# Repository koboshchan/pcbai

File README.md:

pcbai is an analog MNIST classifier built from discrete PCB neural-network boards.

boards/ contains only the final paid v2 sources, matching fabrication ZIPs and the current ADS carrier v3. boards/SHA256.json records exact source hashes. DC1 is four-layer and universal; build four copies using its separate DC1a through DC1d population CSVs. boards/bom/ holds the current assembly data and CSVs.

The motherboard needs the mandatory bottom bodge wire from JS1 B7 at (18.25, 44.27) mm to JS2 B7 at (18.25, 55.27) mm. Fit it before powering the stack. See boards/README.md for release-source and model-path notes.

scripts/ holds the current fabrication exporter, dimensions audit, corrected overlay utilities, BOM PDF builder and paid-board emulator harness. training/ holds MNIST training code, model checkpoints, layer weights, physical-model evaluations and required provenance inputs. The emulator itself lives separately at https://github.com/koboshchan/pcb-emu and is not vendored here.

renders/ contains current board images and the final v2 stack renders. pdfs/ contains the current BOM, corrected normal and clockwise/text-upright overview overlays, motherboard placement input and ADS etch mask. footprints/, 3dmodels/ and fp-lib-table retain the custom connector assets.

Old designs, routing experiments and stale outputs were deleted from the working tree, not archived. They remain available in Git history.

Run heavy training, simulation, CAD exports and rendering on KAT-BOX only. Generated output goes under ignored out/. Release sources and paid fabrication ZIPs are never overwritten by the exporter.

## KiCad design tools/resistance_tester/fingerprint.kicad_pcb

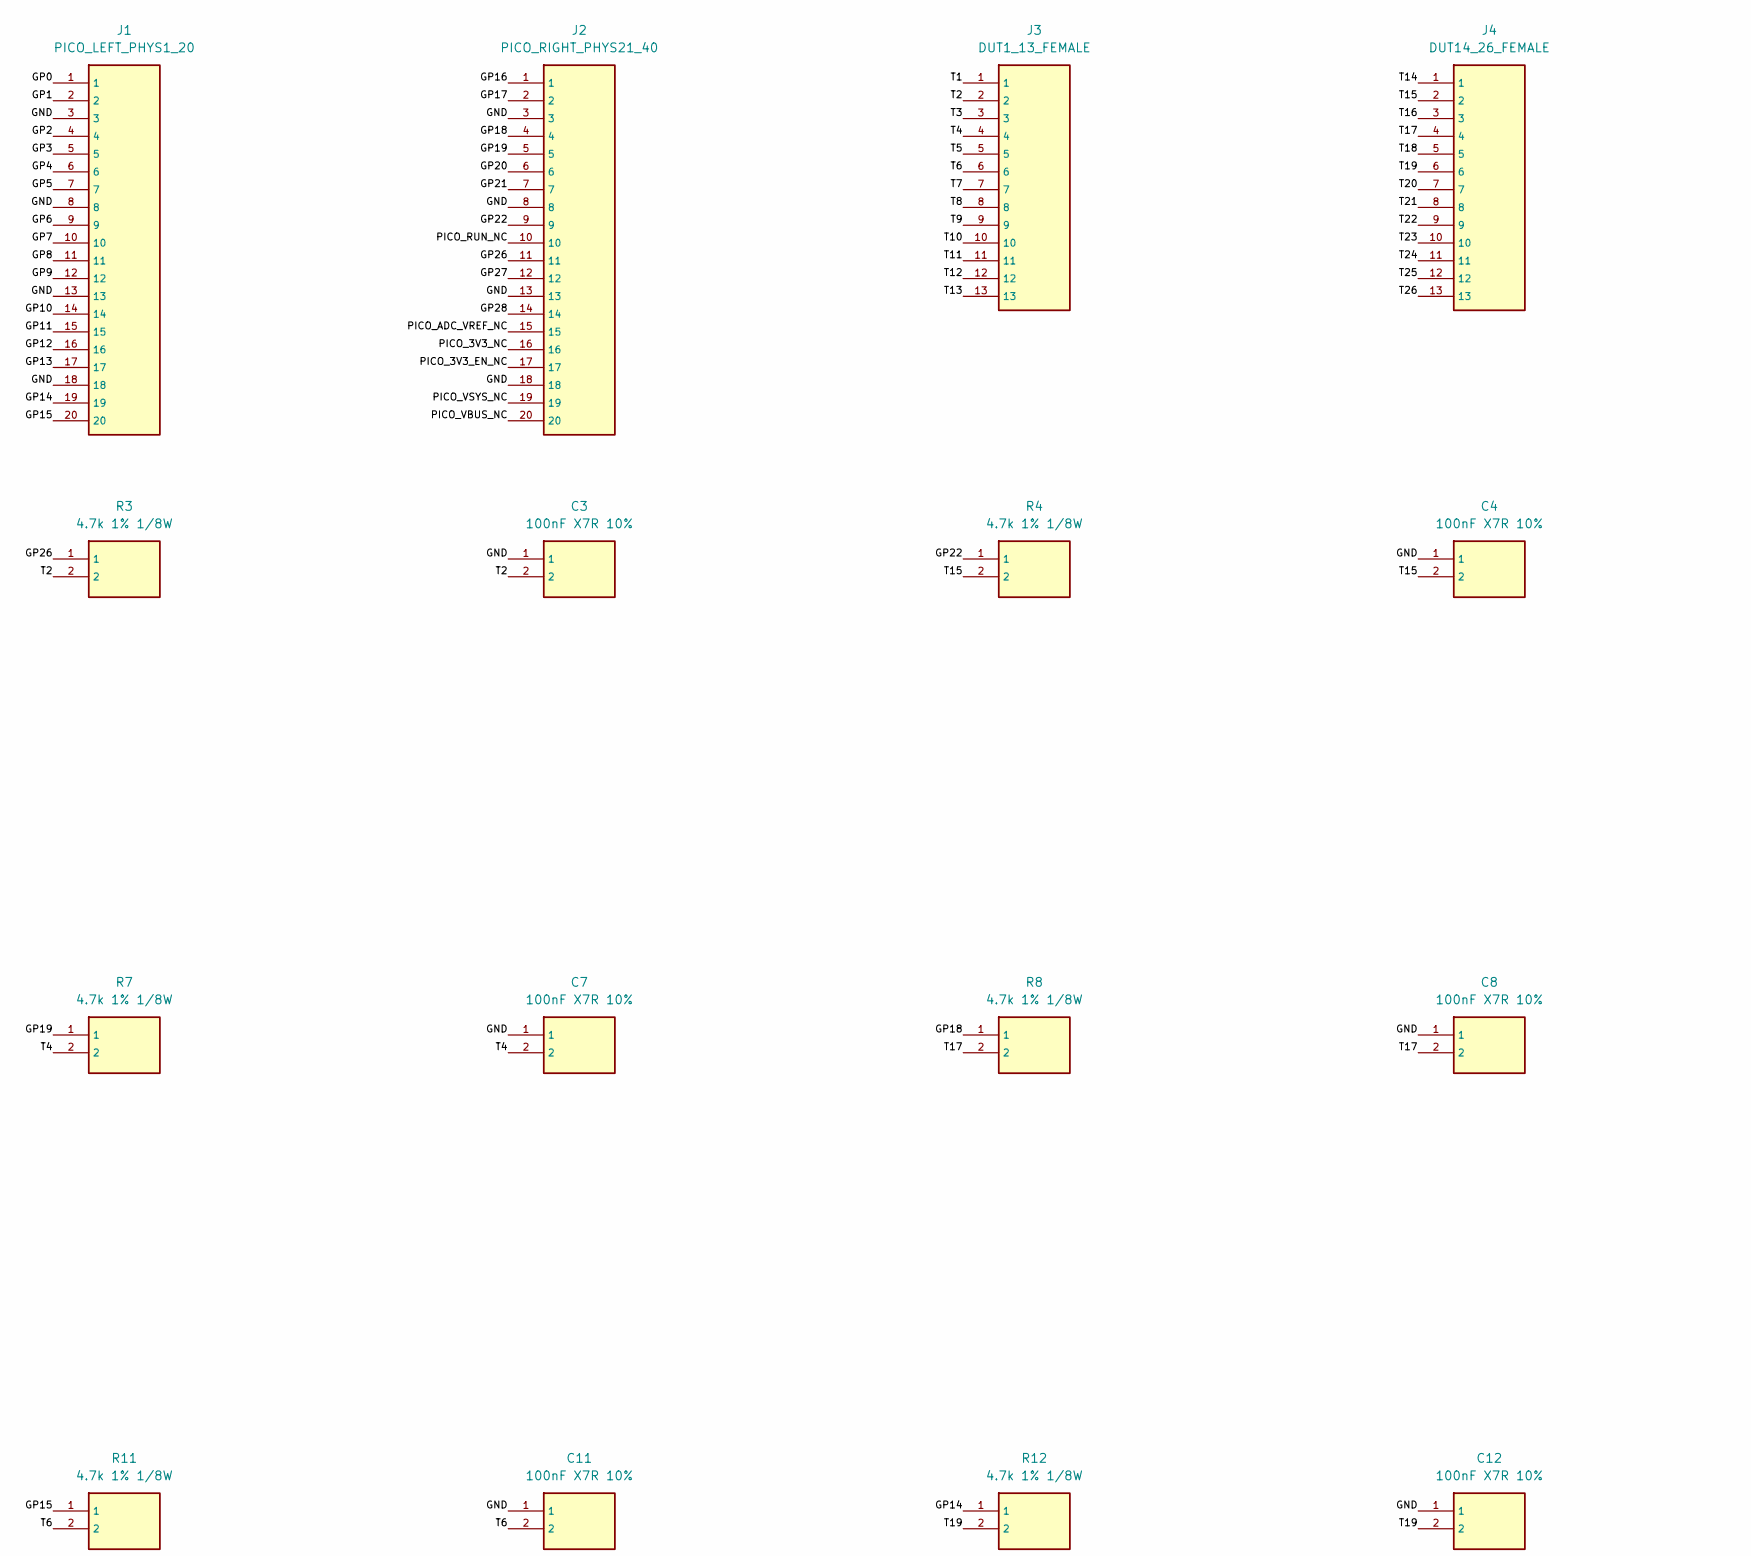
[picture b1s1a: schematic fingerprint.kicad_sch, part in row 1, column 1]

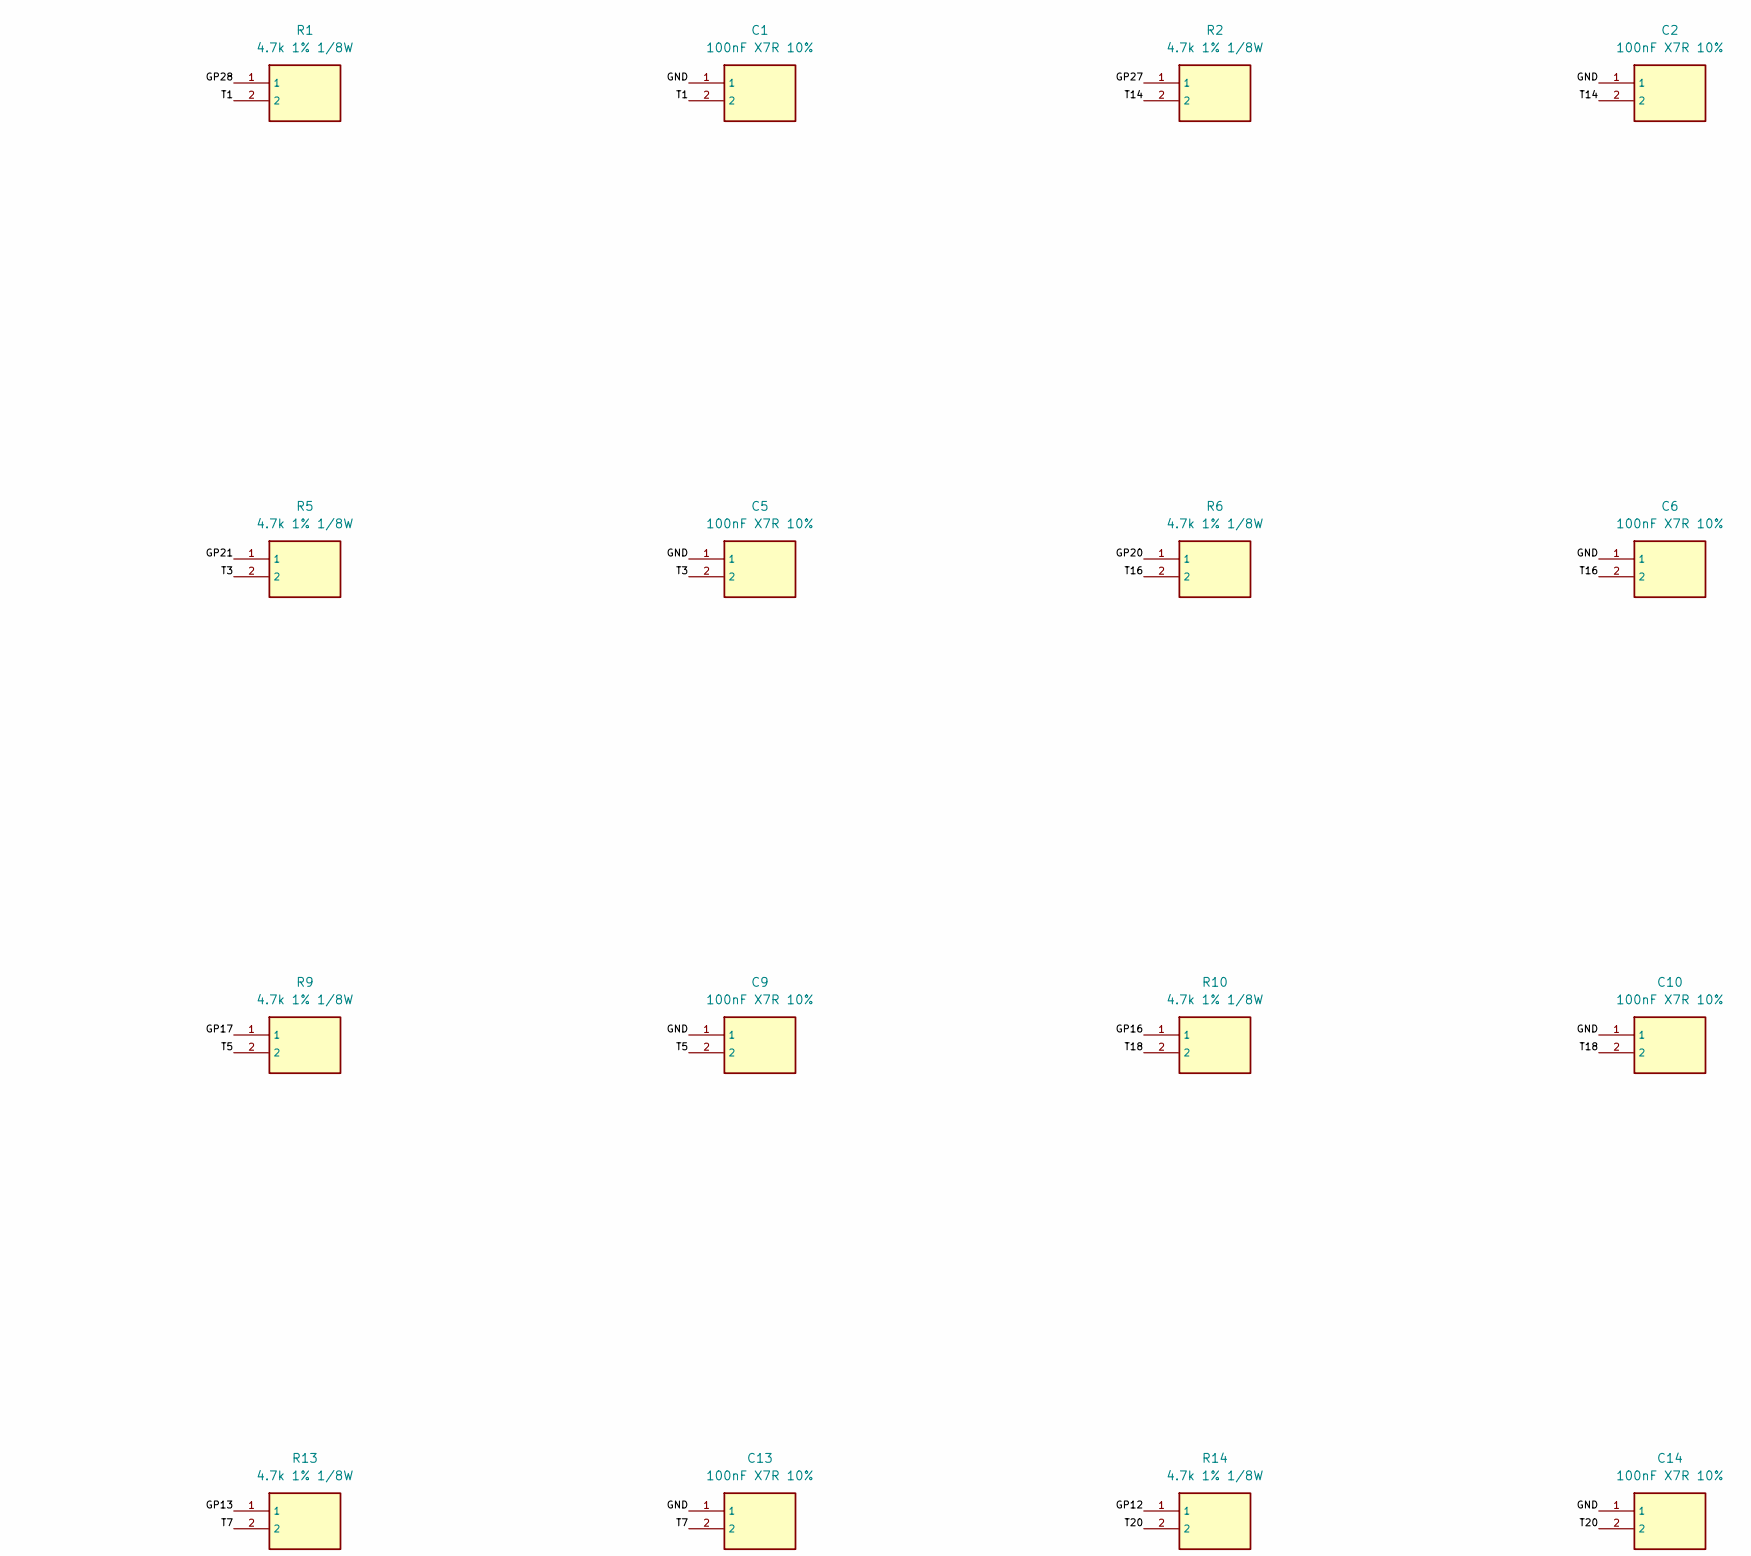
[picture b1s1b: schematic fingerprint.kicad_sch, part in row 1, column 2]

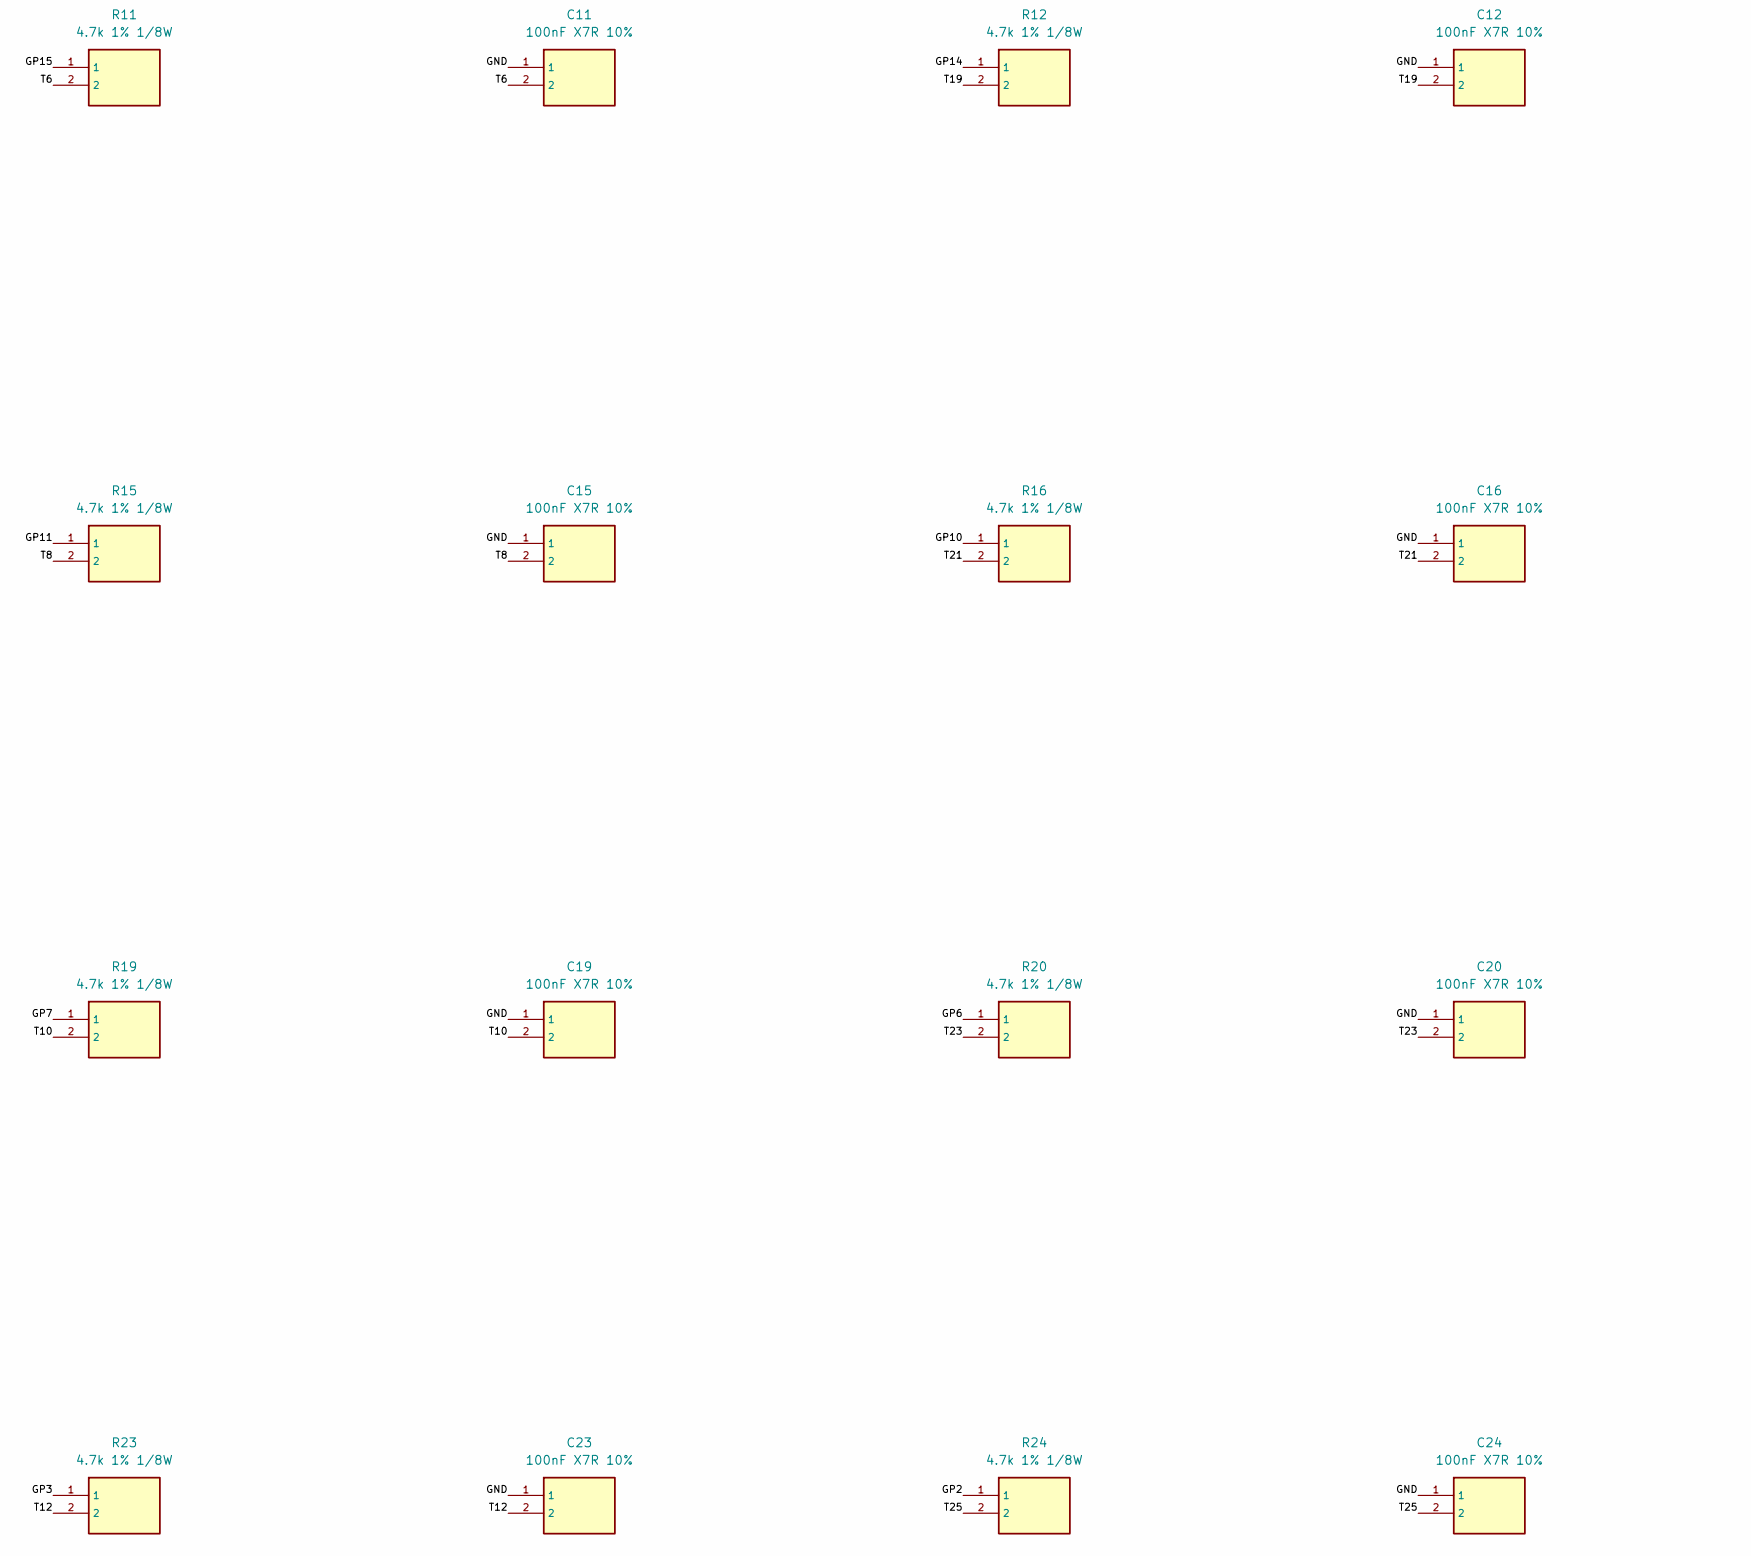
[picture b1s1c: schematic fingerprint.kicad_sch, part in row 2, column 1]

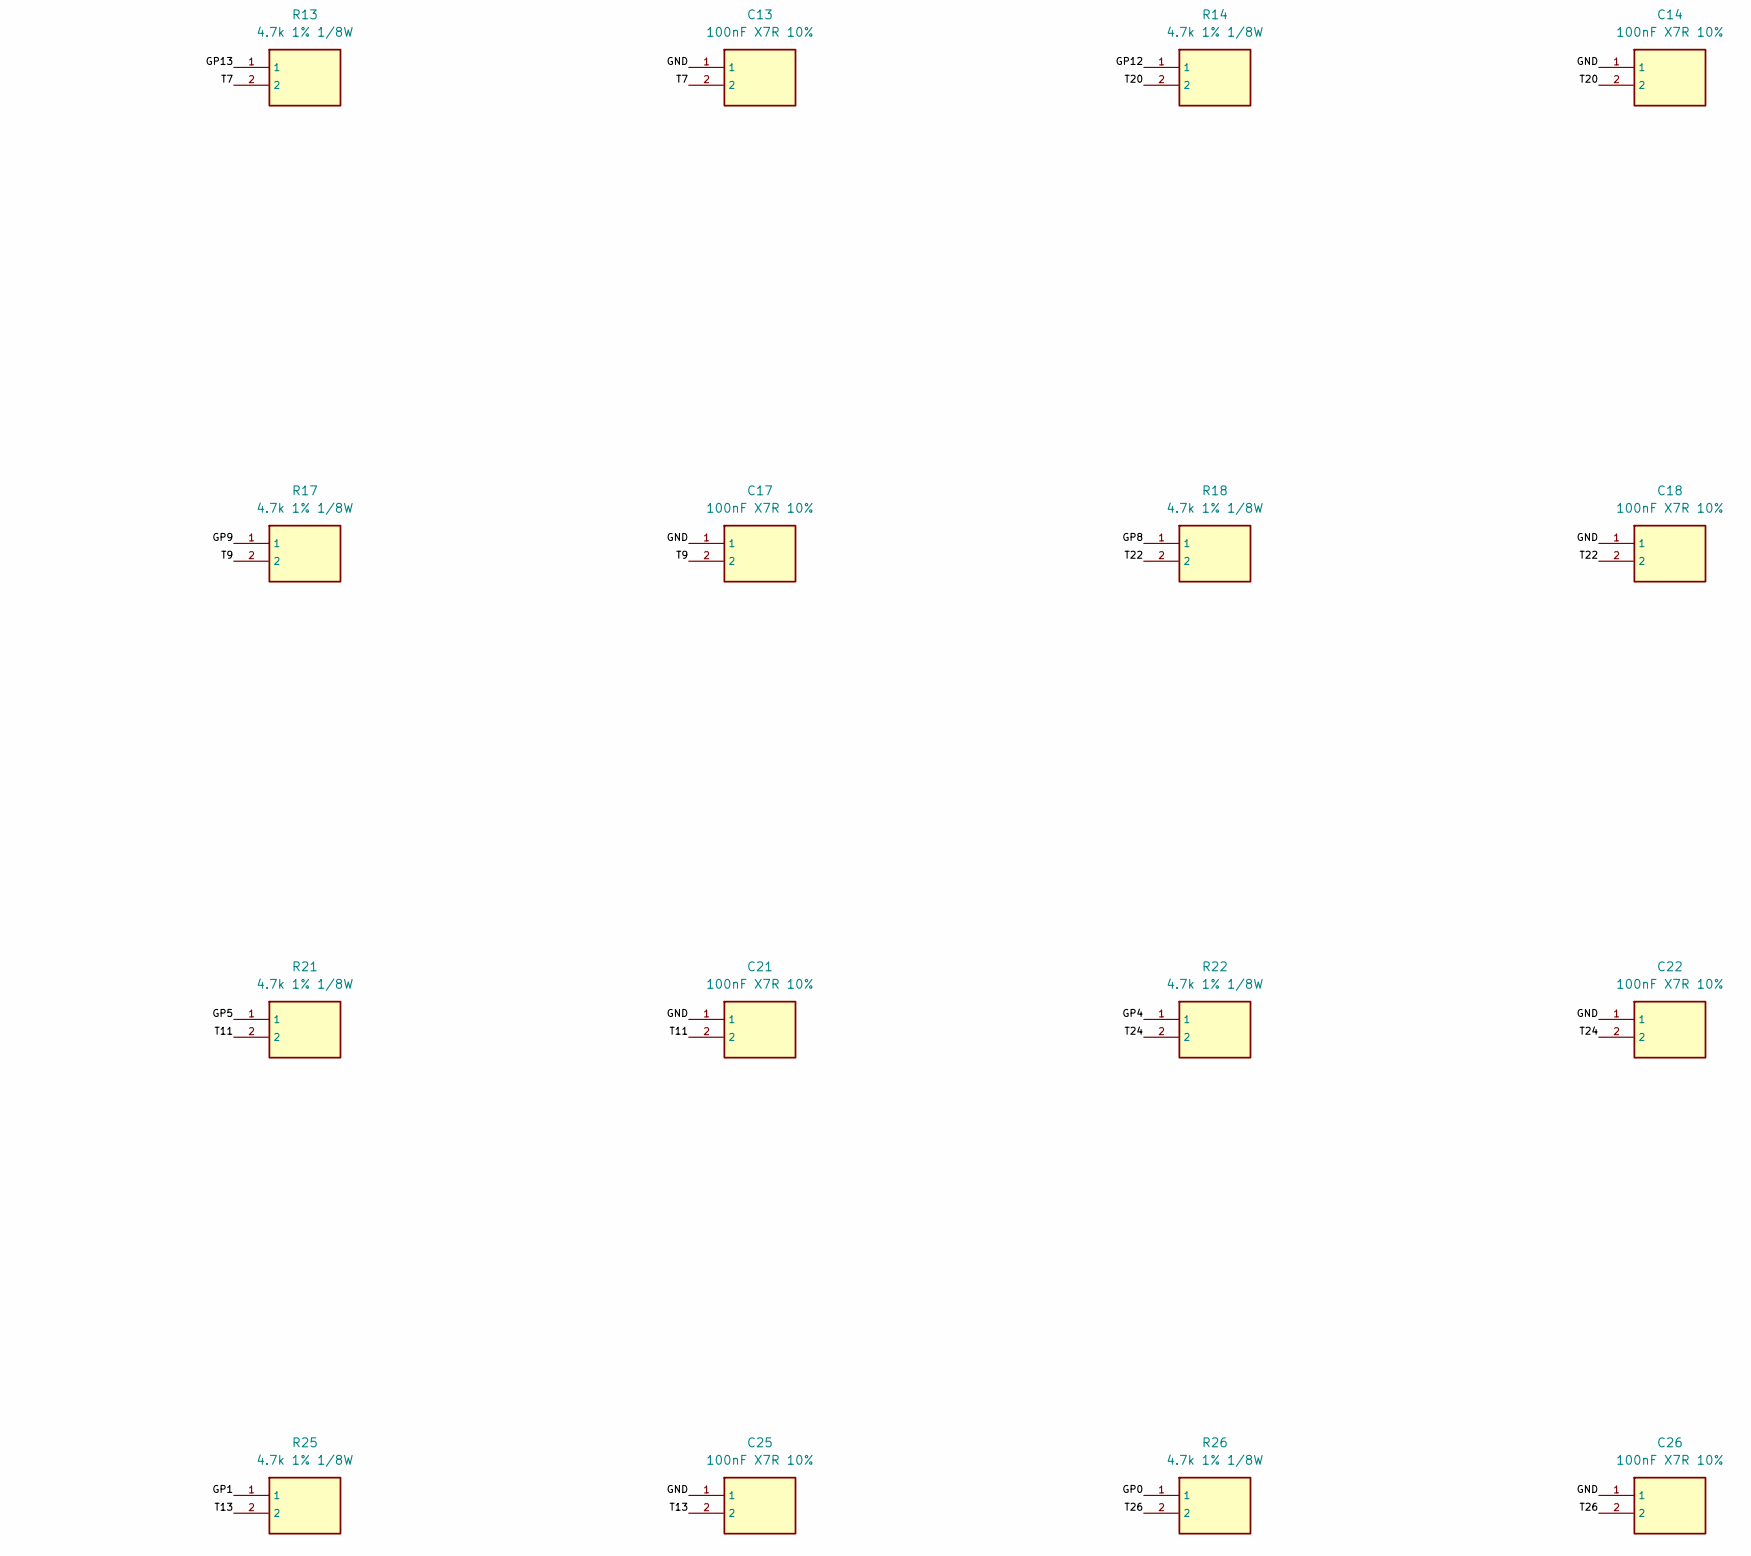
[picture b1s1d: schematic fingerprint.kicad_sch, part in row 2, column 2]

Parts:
C1, C2, C3, C4, C5, C6, C7, C8, C9, C10, C11, C12, C13, C14, C15, C16, C17, C18, C19, C20, C21, C22, C23, C24, C25, C26: 100nF X7R 10%; C_0805_2012Metric
J1: PICO_LEFT_PHYS1_20; Pico_1x20_female_oval_1.7x1.4 (embedded, rectangular pin 1)
J2: PICO_RIGHT_PHYS21_40; Pico_1x20_female_oval_1.7x1.4 (embedded, rectangular pin 1)
J3: DUT1_13_FEMALE; PinSocket_1x13_P2.54mm_Vertical_2x13_block_modified (embedd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
J4: DUT14_26_FEMALE; PinSocket_1x13_P2.54mm_Vertical_2x13_block_modified (embedd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
R1, R2, R3, R4, R5, R6, R7, R8, R9, R10, R11, R12, R13, R14, R15, R16, R17, R18, R19, R20, R21, R22, R23, R24, R25, R26: 4.7k 1% 1/8W; R_0805_2012Metric

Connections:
GND: C1.1, C2.1, C3.1, C4.1, C5.1, C6.1, C7.1, C8.1, C9.1, C10.1, C11.1, C12.1, C13.1, C14.1, C15.1, C16.1, C17.1, C18.1, C19.1, C20.1, C21.1, C22.1, C23.1, C24.1, C25.1, C26.1, J1.3, J1.8, J1.13, J1.18, J2.3, J2.8, J2.13, J2.18
GP0: J1.1, R26.1
GP1: J1.2, R25.1
GP2: J1.4, R24.1
GP3: J1.5, R23.1
GP4: J1.6, R22.1
GP5: J1.7, R21.1
GP6: J1.9, R20.1
GP7: J1.10, R19.1
GP8: J1.11, R18.1
GP9: J1.12, R17.1
GP10: J1.14, R16.1
GP11: J1.15, R15.1
GP12: J1.16, R14.1
GP13: J1.17, R13.1
GP14: J1.19, R12.1
GP15: J1.20, R11.1
GP16: J2.1, R10.1
GP17: J2.2, R9.1
GP18: J2.4, R8.1
GP19: J2.5, R7.1
GP20: J2.6, R6.1
GP21: J2.7, R5.1
GP22: J2.9, R4.1
GP26: J2.11, R3.1
GP27: J2.12, R2.1
GP28: J2.14, R1.1
PICO_3V3_EN_NC: J2.17
PICO_3V3_NC: J2.16
PICO_ADC_VREF_NC: J2.15
PICO_RUN_NC: J2.10
PICO_VBUS_NC: J2.20
PICO_VSYS_NC: J2.19
T1: C1.2, J3.1, R1.2
T2: C3.2, J3.2, R3.2
T3: C5.2, J3.3, R5.2
T4: C7.2, J3.4, R7.2
T5: C9.2, J3.5, R9.2
T6: C11.2, J3.6, R11.2
T7: C13.2, J3.7, R13.2
T8: C15.2, J3.8, R15.2
T9: C17.2, J3.9, R17.2
T10: C19.2, J3.10, R19.2
T11: C21.2, J3.11, R21.2
T12: C23.2, J3.12, R23.2
T13: C25.2, J3.13, R25.2
T14: C2.2, J4.1, R2.2
T15: C4.2, J4.2, R4.2
T16: C6.2, J4.3, R6.2
T17: C8.2, J4.4, R8.2
T18: C10.2, J4.5, R10.2
T19: C12.2, J4.6, R12.2
T20: C14.2, J4.7, R14.2
T21: C16.2, J4.8, R16.2
T22: C18.2, J4.9, R18.2
T23: C20.2, J4.10, R20.2
T24: C22.2, J4.11, R22.2
T25: C24.2, J4.12, R24.2
T26: C26.2, J4.13, R26.2

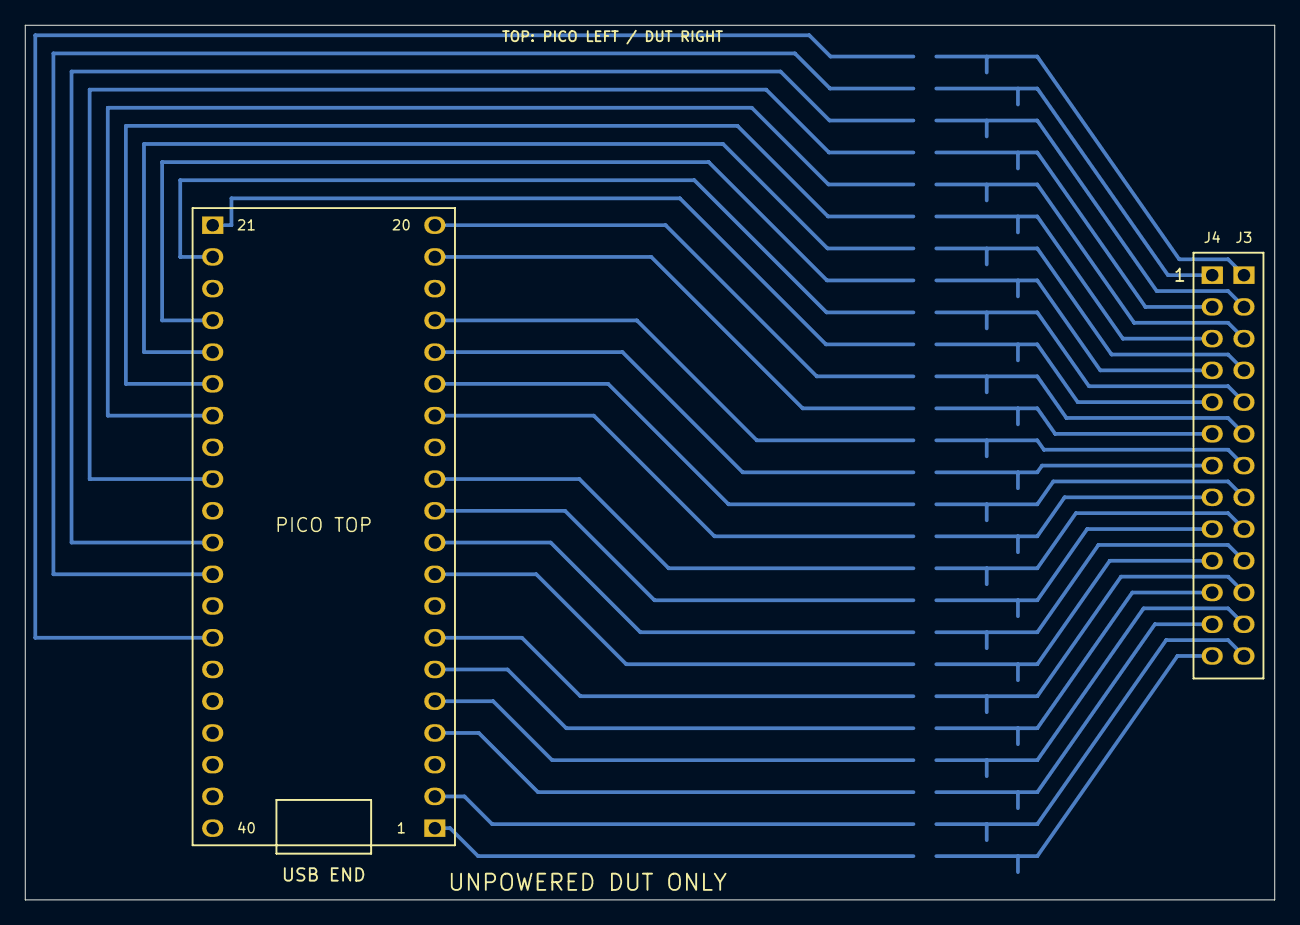
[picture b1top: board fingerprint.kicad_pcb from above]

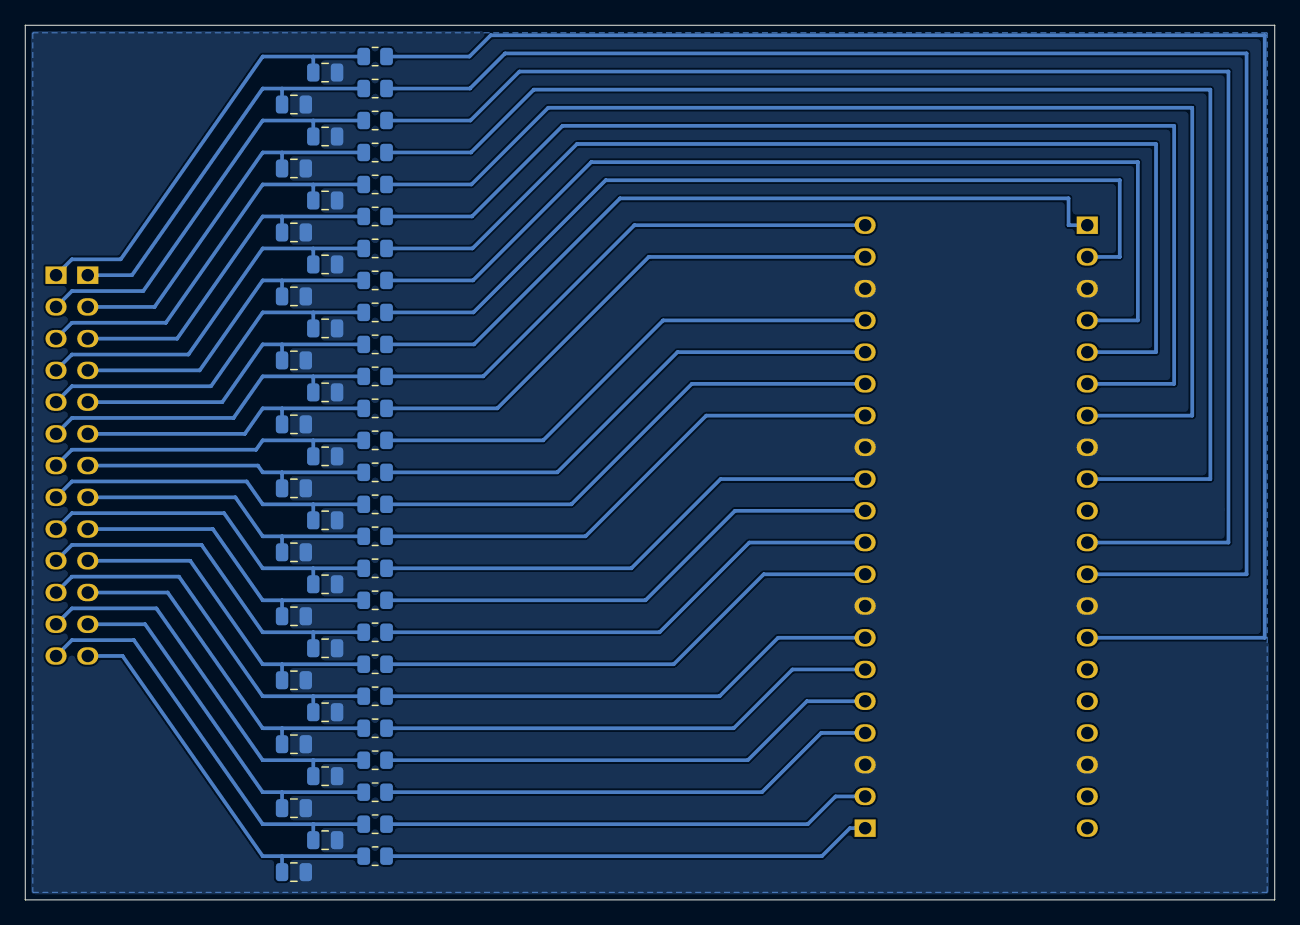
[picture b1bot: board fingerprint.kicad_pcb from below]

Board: 2 copper layers, 100.0 x 70.0 mm, 56 parts (52 on the bottom side), 53 nets.

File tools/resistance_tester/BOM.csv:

Reference,Value,Footprint,Side
J1,PICO_LEFT_PHYS1_20,"Pico_1x20_female_oval_1.7x1.4 (embedded, rectangular pin 1)",Top
J2,PICO_RIGHT_PHYS21_40,"Pico_1x20_female_oval_1.7x1.4 (embedded, rectangular pin 1)",Top
J3,DUT1_13_FEMALE,"PinSocket_1x13_P2.54mm_Vertical_2x13_block_modified (embedded, shared 2x13 silk box, abutting courtyards)",Top
J4,DUT14_26_FEMALE,"PinSocket_1x13_P2.54mm_Vertical_2x13_block_modified (embedded, shared 2x13 silk box, abutting courtyards)",Top
R1,4.7k 1% 1/8W,Resistor_SMD:R_0805_2012Metric,Bottom
C1,100nF X7R 10%,Capacitor_SMD:C_0805_2012Metric,Bottom
R2,4.7k 1% 1/8W,Resistor_SMD:R_0805_2012Metric,Bottom
C2,100nF X7R 10%,Capacitor_SMD:C_0805_2012Metric,Bottom
R3,4.7k 1% 1/8W,Resistor_SMD:R_0805_2012Metric,Bottom
C3,100nF X7R 10%,Capacitor_SMD:C_0805_2012Metric,Bottom
R4,4.7k 1% 1/8W,Resistor_SMD:R_0805_2012Metric,Bottom
C4,100nF X7R 10%,Capacitor_SMD:C_0805_2012Metric,Bottom
R5,4.7k 1% 1/8W,Resistor_SMD:R_0805_2012Metric,Bottom
C5,100nF X7R 10%,Capacitor_SMD:C_0805_2012Metric,Bottom
R6,4.7k 1% 1/8W,Resistor_SMD:R_0805_2012Metric,Bottom
C6,100nF X7R 10%,Capacitor_SMD:C_0805_2012Metric,Bottom
R7,4.7k 1% 1/8W,Resistor_SMD:R_0805_2012Metric,Bottom
C7,100nF X7R 10%,Capacitor_SMD:C_0805_2012Metric,Bottom
R8,4.7k 1% 1/8W,Resistor_SMD:R_0805_2012Metric,Bottom
C8,100nF X7R 10%,Capacitor_SMD:C_0805_2012Metric,Bottom
R9,4.7k 1% 1/8W,Resistor_SMD:R_0805_2012Metric,Bottom
C9,100nF X7R 10%,Capacitor_SMD:C_0805_2012Metric,Bottom
R10,4.7k 1% 1/8W,Resistor_SMD:R_0805_2012Metric,Bottom
C10,100nF X7R 10%,Capacitor_SMD:C_0805_2012Metric,Bottom
R11,4.7k 1% 1/8W,Resistor_SMD:R_0805_2012Metric,Bottom
C11,100nF X7R 10%,Capacitor_SMD:C_0805_2012Metric,Bottom
R12,4.7k 1% 1/8W,Resistor_SMD:R_0805_2012Metric,Bottom
C12,100nF X7R 10%,Capacitor_SMD:C_0805_2012Metric,Bottom
R13,4.7k 1% 1/8W,Resistor_SMD:R_0805_2012Metric,Bottom
C13,100nF X7R 10%,Capacitor_SMD:C_0805_2012Metric,Bottom
R14,4.7k 1% 1/8W,Resistor_SMD:R_0805_2012Metric,Bottom
C14,100nF X7R 10%,Capacitor_SMD:C_0805_2012Metric,Bottom
R15,4.7k 1% 1/8W,Resistor_SMD:R_0805_2012Metric,Bottom
C15,100nF X7R 10%,Capacitor_SMD:C_0805_2012Metric,Bottom
R16,4.7k 1% 1/8W,Resistor_SMD:R_0805_2012Metric,Bottom
C16,100nF X7R 10%,Capacitor_SMD:C_0805_2012Metric,Bottom
R17,4.7k 1% 1/8W,Resistor_SMD:R_0805_2012Metric,Bottom
C17,100nF X7R 10%,Capacitor_SMD:C_0805_2012Metric,Bottom
R18,4.7k 1% 1/8W,Resistor_SMD:R_0805_2012Metric,Bottom
C18,100nF X7R 10%,Capacitor_SMD:C_0805_2012Metric,Bottom
R19,4.7k 1% 1/8W,Resistor_SMD:R_0805_2012Metric,Bottom
C19,100nF X7R 10%,Capacitor_SMD:C_0805_2012Metric,Bottom
R20,4.7k 1% 1/8W,Resistor_SMD:R_0805_2012Metric,Bottom
C20,100nF X7R 10%,Capacitor_SMD:C_0805_2012Metric,Bottom
R21,4.7k 1% 1/8W,Resistor_SMD:R_0805_2012Metric,Bottom
C21,100nF X7R 10%,Capacitor_SMD:C_0805_2012Metric,Bottom
R22,4.7k 1% 1/8W,Resistor_SMD:R_0805_2012Metric,Bottom
C22,100nF X7R 10%,Capacitor_SMD:C_0805_2012Metric,Bottom
R23,4.7k 1% 1/8W,Resistor_SMD:R_0805_2012Metric,Bottom
C23,100nF X7R 10%,Capacitor_SMD:C_0805_2012Metric,Bottom
R24,4.7k 1% 1/8W,Resistor_SMD:R_0805_2012Metric,Bottom
C24,100nF X7R 10%,Capacitor_SMD:C_0805_2012Metric,Bottom
R25,4.7k 1% 1/8W,Resistor_SMD:R_0805_2012Metric,Bottom
C25,100nF X7R 10%,Capacitor_SMD:C_0805_2012Metric,Bottom
R26,4.7k 1% 1/8W,Resistor_SMD:R_0805_2012Metric,Bottom
C26,100nF X7R 10%,Capacitor_SMD:C_0805_2012Metric,Bottom

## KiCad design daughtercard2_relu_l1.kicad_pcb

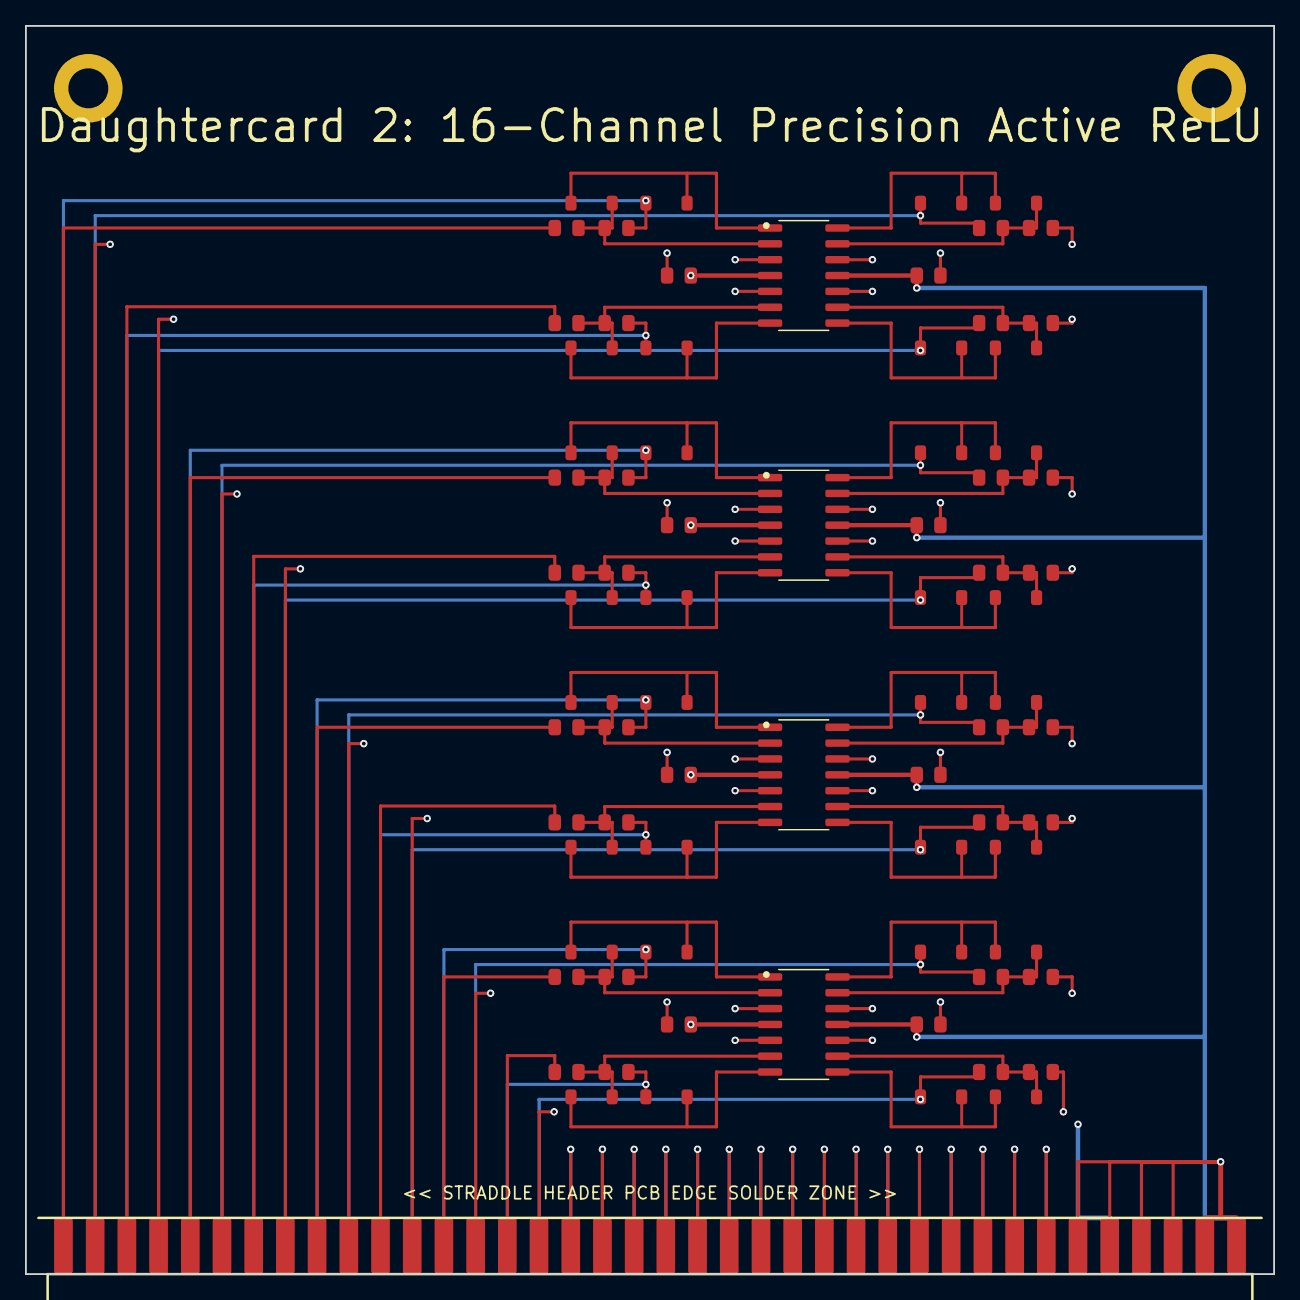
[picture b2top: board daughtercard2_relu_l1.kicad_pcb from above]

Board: 4 copper layers, 100.0 x 100.0 mm, 79 parts (0 on the bottom side), 67 nets.

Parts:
C_U1N, C_U1P, C_U2N, C_U2P, C_U3N, C_U3P, C_U4N, C_U4P: 0.1uF; C_0805_2012Metric
D_CLAMP_0, D_CLAMP_1, D_CLAMP_2, D_CLAMP_3, D_CLAMP_4, D_CLAMP_5, D_CLAMP_6, D_CLAMP_7, D_CLAMP_8, D_CLAMP_9, D_CLAMP_10, D_CLAMP_11, D_CLAMP_12, D_CLAMP_13, D_CLAMP_14, D_CLAMP_15: 1N4148; D_SOD-123
D_RECT_0, D_RECT_1, D_RECT_2, D_RECT_3, D_RECT_4, D_RECT_5, D_RECT_6, D_RECT_7, D_RECT_8, D_RECT_9, D_RECT_10, D_RECT_11, D_RECT_12, D_RECT_13, D_RECT_14, D_RECT_15: 1N4148; D_SOD-123
H1, H2: MountingHole; MountingHole_3.2mm_M3_Pad
J_STRADDLE_EDGE: PinHeader_2x38_Straddle; PinHeader_2x38_Straddle_P2.54mm
R_FB_0, R_FB_1, R_FB_2, R_FB_3, R_FB_4, R_FB_5, R_FB_6, R_FB_7, R_FB_8, R_FB_9, R_FB_10, R_FB_11, R_FB_12, R_FB_13, R_FB_14, R_FB_15: 10k; R_0805_2012Metric
R_IN_0, R_IN_1, R_IN_2, R_IN_3, R_IN_4, R_IN_5, R_IN_6, R_IN_7, R_IN_8, R_IN_9, R_IN_10, R_IN_11, R_IN_12, R_IN_13, R_IN_14, R_IN_15: 10k; R_0805_2012Metric
U1, U2, U3, U4: TL074; SOIC-14_3.9x8.7mm_P1.27mm

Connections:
+12V: C_U1P.2, C_U2P.2, C_U3P.2, C_U4P.2, J_STRADDLE_EDGE.B33, J_STRADDLE_EDGE.B34, U1.4, U2.4, U3.4, U4.4
-12V: C_U1N.1, C_U2N.1, C_U3N.1, C_U4N.1, J_STRADDLE_EDGE.B37, J_STRADDLE_EDGE.B38, U1.11, U2.11, U3.11, U4.11
ACT_0: D_RECT_0.1, J_STRADDLE_EDGE.B1, R_FB_0.2
ACT_1: D_RECT_1.1, J_STRADDLE_EDGE.B2, R_FB_1.1
ACT_2: D_RECT_2.1, J_STRADDLE_EDGE.B3, R_FB_2.2
ACT_3: D_RECT_3.1, J_STRADDLE_EDGE.B4, R_FB_3.1
ACT_4: D_RECT_4.1, J_STRADDLE_EDGE.B5, R_FB_4.2
ACT_5: D_RECT_5.1, J_STRADDLE_EDGE.B6, R_FB_5.1
ACT_6: D_RECT_6.1, J_STRADDLE_EDGE.B7, R_FB_6.2
ACT_7: D_RECT_7.1, J_STRADDLE_EDGE.B8, R_FB_7.1
ACT_8: D_RECT_8.1, J_STRADDLE_EDGE.B9, R_FB_8.2
ACT_9: D_RECT_9.1, J_STRADDLE_EDGE.B10, R_FB_9.1
ACT_10: D_RECT_10.1, J_STRADDLE_EDGE.B11, R_FB_10.2
ACT_11: D_RECT_11.1, J_STRADDLE_EDGE.B12, R_FB_11.1
ACT_12: D_RECT_12.1, J_STRADDLE_EDGE.B13, R_FB_12.2
ACT_13: D_RECT_13.1, J_STRADDLE_EDGE.B14, R_FB_13.1
ACT_14: D_RECT_14.1, J_STRADDLE_EDGE.B15, R_FB_14.2
ACT_15: D_RECT_15.1, J_STRADDLE_EDGE.B16, R_FB_15.1
GND: C_U1N.2, C_U1P.1, C_U2N.2, C_U2P.1, C_U3N.2, C_U3P.1, C_U4N.2, C_U4P.1, H1.1, H2.1, J_STRADDLE_EDGE.A17, J_STRADDLE_EDGE.A18, J_STRADDLE_EDGE.A19, J_STRADDLE_EDGE.A20, J_STRADDLE_EDGE.A21, J_STRADDLE_EDGE.A22, J_STRADDLE_EDGE.A23, J_STRADDLE_EDGE.A24, J_STRADDLE_EDGE.A25, J_STRADDLE_EDGE.A26, J_STRADDLE_EDGE.A27, J_STRADDLE_EDGE.A28, J_STRADDLE_EDGE.A29, J_STRADDLE_EDGE.A30, J_STRADDLE_EDGE.A31, J_STRADDLE_EDGE.A32, J_STRADDLE_EDGE.A33, J_STRADDLE_EDGE.A34, J_STRADDLE_EDGE.A35, J_STRADDLE_EDGE.A36, J_STRADDLE_EDGE.A37, J_STRADDLE_EDGE.A38, J_STRADDLE_EDGE.B17, J_STRADDLE_EDGE.B18, J_STRADDLE_EDGE.B19, J_STRADDLE_EDGE.B20, J_STRADDLE_EDGE.B21, J_STRADDLE_EDGE.B22, J_STRADDLE_EDGE.B23, J_STRADDLE_EDGE.B24, J_STRADDLE_EDGE.B25, J_STRADDLE_EDGE.B26, J_STRADDLE_EDGE.B27, J_STRADDLE_EDGE.B28, J_STRADDLE_EDGE.B29, J_STRADDLE_EDGE.B30, J_STRADDLE_EDGE.B31, J_STRADDLE_EDGE.B32, U1.3, U1.5, U1.10, U1.12, U2.3, U2.5, U2.10, U2.12, U3.3, U3.5, U3.10, U3.12, U4.3, U4.5, U4.10, U4.12
INV_RELU_0: D_CLAMP_0.2, R_FB_0.1, R_IN_0.2, U1.2
INV_RELU_1: D_CLAMP_1.2, R_FB_1.2, R_IN_1.1, U1.13
INV_RELU_2: D_CLAMP_2.2, R_FB_2.1, R_IN_2.2, U1.6
INV_RELU_3: D_CLAMP_3.2, R_FB_3.2, R_IN_3.1, U1.9
INV_RELU_4: D_CLAMP_4.2, R_FB_4.1, R_IN_4.2, U2.2
INV_RELU_5: D_CLAMP_5.2, R_FB_5.2, R_IN_5.1, U2.13
INV_RELU_6: D_CLAMP_6.2, R_FB_6.1, R_IN_6.2, U2.6
INV_RELU_7: D_CLAMP_7.2, R_FB_7.2, R_IN_7.1, U2.9
INV_RELU_8: D_CLAMP_8.2, R_FB_8.1, R_IN_8.2, U3.2
INV_RELU_9: D_CLAMP_9.2, R_FB_9.2, R_IN_9.1, U3.13
INV_RELU_10: D_CLAMP_10.2, R_FB_10.1, R_IN_10.2, U3.6
INV_RELU_11: D_CLAMP_11.2, R_FB_11.2, R_IN_11.1, U3.9
INV_RELU_12: D_CLAMP_12.2, R_FB_12.1, R_IN_12.2, U4.2
INV_RELU_13: D_CLAMP_13.2, R_FB_13.2, R_IN_13.1, U4.13
INV_RELU_14: D_CLAMP_14.2, R_FB_14.1, R_IN_14.2, U4.6
INV_RELU_15: D_CLAMP_15.2, R_FB_15.2, R_IN_15.1, U4.9
OP_OUT_0: D_CLAMP_0.1, D_RECT_0.2, U1.1
OP_OUT_1: D_CLAMP_1.1, D_RECT_1.2, U1.14
OP_OUT_2: D_CLAMP_2.1, D_RECT_2.2, U1.7
OP_OUT_3: D_CLAMP_3.1, D_RECT_3.2, U1.8
OP_OUT_4: D_CLAMP_4.1, D_RECT_4.2, U2.1
OP_OUT_5: D_CLAMP_5.1, D_RECT_5.2, U2.14
OP_OUT_6: D_CLAMP_6.1, D_RECT_6.2, U2.7
OP_OUT_7: D_CLAMP_7.1, D_RECT_7.2, U2.8
OP_OUT_8: D_CLAMP_8.1, D_RECT_8.2, U3.1
OP_OUT_9: D_CLAMP_9.1, D_RECT_9.2, U3.14
OP_OUT_10: D_CLAMP_10.1, D_RECT_10.2, U3.7
OP_OUT_11: D_CLAMP_11.1, D_RECT_11.2, U3.8
OP_OUT_12: D_CLAMP_12.1, D_RECT_12.2, U4.1
OP_OUT_13: D_CLAMP_13.1, D_RECT_13.2, U4.14
OP_OUT_14: D_CLAMP_14.1, D_RECT_14.2, U4.7
OP_OUT_15: D_CLAMP_15.1, D_RECT_15.2, U4.8
V_SUM_0: J_STRADDLE_EDGE.A1, R_IN_0.1
V_SUM_1: J_STRADDLE_EDGE.A2, R_IN_1.2
V_SUM_2: J_STRADDLE_EDGE.A3, R_IN_2.1
V_SUM_3: J_STRADDLE_EDGE.A4, R_IN_3.2
V_SUM_4: J_STRADDLE_EDGE.A5, R_IN_4.1
V_SUM_5: J_STRADDLE_EDGE.A6, R_IN_5.2
V_SUM_6: J_STRADDLE_EDGE.A7, R_IN_6.1
V_SUM_7: J_STRADDLE_EDGE.A8, R_IN_7.2
V_SUM_8: J_STRADDLE_EDGE.A9, R_IN_8.1
V_SUM_9: J_STRADDLE_EDGE.A10, R_IN_9.2
V_SUM_10: J_STRADDLE_EDGE.A11, R_IN_10.1
V_SUM_11: J_STRADDLE_EDGE.A12, R_IN_11.2
V_SUM_12: J_STRADDLE_EDGE.A13, R_IN_12.1
V_SUM_13: J_STRADDLE_EDGE.A14, R_IN_13.2
V_SUM_14: J_STRADDLE_EDGE.A15, R_IN_14.1
V_SUM_15: J_STRADDLE_EDGE.A16, R_IN_15.2
